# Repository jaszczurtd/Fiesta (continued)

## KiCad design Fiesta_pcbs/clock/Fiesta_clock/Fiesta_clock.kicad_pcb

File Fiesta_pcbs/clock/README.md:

# Fiesta_clock PCB

[Polski](README.pl.md)

A 70 × 70 mm carrier for RP2040-Zero, CAN and DS3231 Mini. Firmware defaults to a different
RTC, so select the board variant deliberately.

## Before connecting

- Use USB or vehicle power, never both at once.
- Select the DS3231 firmware variant for this board. The default firmware selects PCF8563.
- R9/R10 are 47 kΩ / 10 kΩ; the firmware voltage conversion still needs the corresponding update.
- Check regulator temperature, supply stability, RTC header orientation and battery arrangement on the prototype.

## Assembly and startup

The [assembly reference](ASSEMBLY.md) contains schematics, previews, connectors, component
selection and manufacturing requirements. It uses the KiCad project names and numbering.

After checking the hardware, follow the [firmware guide](../../src/Fiesta_clock/README.md).

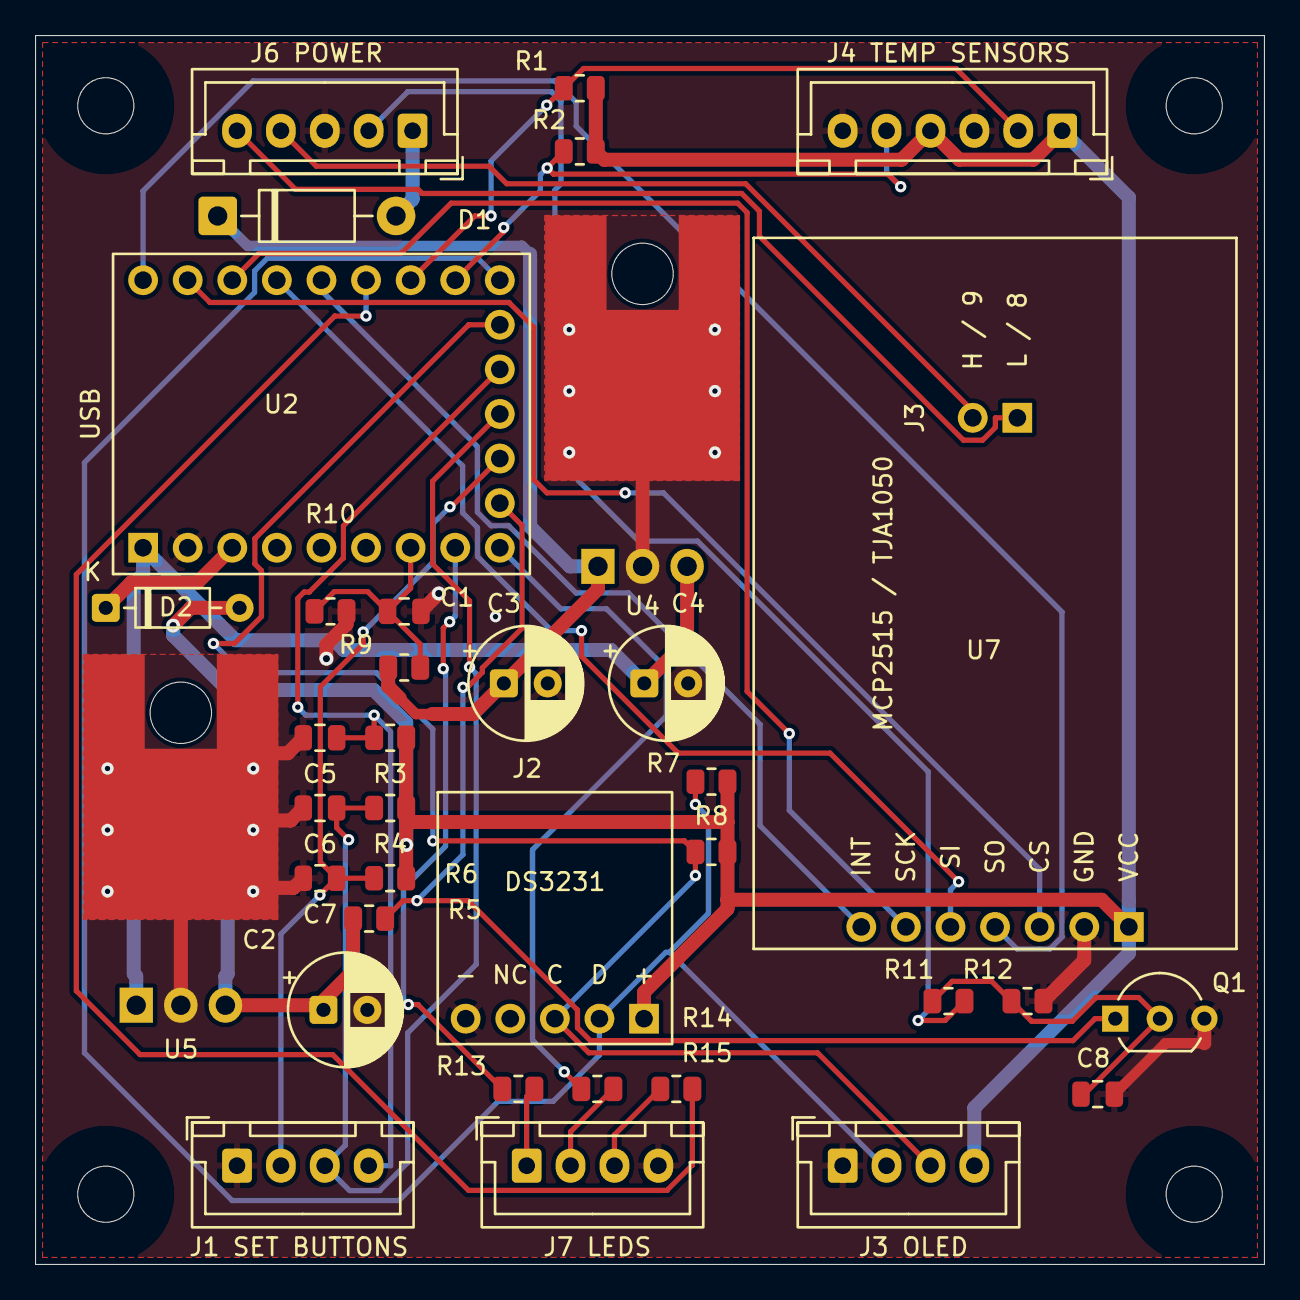
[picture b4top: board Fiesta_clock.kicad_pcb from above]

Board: 2 copper layers, 70.0 x 70.0 mm, 40 parts (0 on the bottom side), 30 nets.

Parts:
C1, C5, C6, C7, C8: 100nF; C_0805_2012Metric
C2, C3, C4: 4,7uF; CP_Radial_D6.3mm_P2.50mm
D1: 1N4007; D_DO-41_SOD81_P10.16mm_Horizontal
D2: BAT48RL; D_DO-35_SOD27_P7.62mm_Horizontal
H1, H2, H3, H4: MountingHole_3.2mm_M3
J1: Set-buttons; JST_XH_B4B-XH-A_1x04_P2.50mm_Vertical
J2: DS3231 Mini; DS3231_Mini_13x14mm_1x05_P2.54mm
J3: OLED module; JST_XH_B4B-XH-A_1x04_P2.50mm_Vertical
J4: temp-sensors; JST_XH_B6B-XH-A_1x06_P2.50mm_Vertical
J6: Power; JST_XH_B5B-XH-A_1x05_P2.50mm_Vertical
J7: LEDs; JST_XH_B4B-XH-A_1x04_P2.50mm_Vertical
Q1: BC547; TO-92_Inline_Wide
R1, R2, R3, R4, R5, R6, R7, R8, R11: 4k7; R_0805_2012Metric
R9: 47k; R_0805_2012Metric
R10, R12: 10k; R_0805_2012Metric
R13, R14, R15: 470R; R_0805_2012Metric
U2: RP2040-Zero; RP2040-Zero_THT
U4: L7805; TO-220-3_Horizontal_TabDown_GND
U5: LM2931-3.3; TO-220-3_Horizontal_TabDown_GND
U7: MCP2515_CAN; MCP2515_TJA1050_Module_J3_40x27mm

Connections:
GND: C1.2, C2.2, C3.2, C4.2, C5.2, C6.2, C7.2, C8.2, J1.1, J2.5, J3.1, J4.3, J4.6, J6.3, J7.4, Q1.3, R10.2, R12.2, U2.2, U4.2, U5.2, U7.2
unnamed: D1.2, J6.1
unnamed: C3.1, D1.1, R9.1, U4.1
unnamed: C2.1, D2.2, J2.1, J3.4, J4.1, J4.4, R1.2, R2.2, R3.1, R4.1, R5.1, R6.1, R7.2, R8.2, U5.3, U7.1
unnamed: D2.1, U2.3
unnamed: C7.1, J1.2, R5.2, U2.20
unnamed: C6.1, J1.3, R4.2, U2.21
unnamed: C5.1, J1.4, R3.2, U2.22
unnamed: J2.3, J3.3, R8.1, U2.23
unnamed: J2.2, J3.2, R7.1, U2.18
unnamed: J4.2, R1.1, U2.16
unnamed: J4.5, R2.1, U2.17
unnamed: J6.2, R11.2
unnamed: J6.4, U7.9
unnamed: J6.5, U7.8
unnamed: J7.1, R13.2
unnamed: J7.2, R14.2
unnamed: J7.3, R15.1
unnamed: C8.1, Q1.2, R11.1, R12.1
unnamed: Q1.1, R6.2, U2.19
unnamed: C4.1, U2.1, U4.3, U5.1
unnamed: U2.10, U7.4
unnamed: U2.11, U7.3
unnamed: U2.12, U7.6
unnamed: U2.13, U7.5
unnamed: U2.14, U7.7
unnamed: R15.2, U2.15
unnamed: R14.1, U2.9
unnamed: R13.1, U2.8
unnamed: C1.1, R9.2, R10.1, U2.7

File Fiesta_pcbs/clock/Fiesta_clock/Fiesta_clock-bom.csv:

"Reference","Value","Footprint","Quantity"
"C1","100nF","Capacitor_SMD:C_0805_2012Metric","1"
"C2","4,7uF","Capacitor_THT:CP_Radial_D6.3mm_P2.50mm","1"
"C3","4,7uF","Capacitor_THT:CP_Radial_D6.3mm_P2.50mm","1"
"C4","4,7uF","Capacitor_THT:CP_Radial_D6.3mm_P2.50mm","1"
"C5","100nF","Capacitor_SMD:C_0805_2012Metric","1"
"C6","100nF","Capacitor_SMD:C_0805_2012Metric","1"
"C7","100nF","Capacitor_SMD:C_0805_2012Metric","1"
"C8","100nF","Capacitor_SMD:C_0805_2012Metric","1"
"D1","1N4007","Diode_THT:D_DO-41_SOD81_P10.16mm_Horizontal","1"
"D2","BAT48RL","Diode_THT:D_DO-35_SOD27_P7.62mm_Horizontal","1"
"J1","Set-buttons","Connector_JST:JST_XH_B4B-XH-A_1x04_P2.50mm_Vertical","1"
"J2","DS3231 Mini","FiestaClock:DS3231_Mini_13x14mm_1x05_P2.54mm","1"
"J3","OLED module","Connector_JST:JST_XH_B4B-XH-A_1x04_P2.50mm_Vertical","1"
"J4","temp-sensors","Connector_JST:JST_XH_B6B-XH-A_1x06_P2.50mm_Vertical","1"
"J6","Power","Connector_JST:JST_XH_B5B-XH-A_1x05_P2.50mm_Vertical","1"
"J7","LEDs","Connector_JST:JST_XH_B4B-XH-A_1x04_P2.50mm_Vertical","1"
"Q1","BC547","Package_TO_SOT_THT:TO-92_Inline_Wide","1"
"R1","4k7","Resistor_SMD:R_0805_2012Metric","1"
"R2","4k7","Resistor_SMD:R_0805_2012Metric","1"
"R3","4k7","Resistor_SMD:R_0805_2012Metric","1"
"R4","4k7","Resistor_SMD:R_0805_2012Metric","1"
"R5","4k7","Resistor_SMD:R_0805_2012Metric","1"
"R6","4k7","Resistor_SMD:R_0805_2012Metric","1"
"R7","4k7","Resistor_SMD:R_0805_2012Metric","1"
"R8","4k7","Resistor_SMD:R_0805_2012Metric","1"
"R9","47k","Resistor_SMD:R_0805_2012Metric","1"
"R10","10k","Resistor_SMD:R_0805_2012Metric","1"
"R11","4k7","Resistor_SMD:R_0805_2012Metric","1"
"R12","10k","Resistor_SMD:R_0805_2012Metric","1"
"R13","470R","Resistor_SMD:R_0805_2012Metric","1"
"R14","470R","Resistor_SMD:R_0805_2012Metric","1"
"R15","470R","Resistor_SMD:R_0805_2012Metric","1"
"U2","RP2040-Zero","Adjustometer:RP2040-Zero_THT","1"
"U4","L7805","FiestaClock:TO-220-3_Horizontal_TabDown_GND","1"
"U5","LM2931-3.3","FiestaClock:TO-220-3_Horizontal_TabDown_GND","1"
"U7","MCP2515_CAN","FiestaFootprints:MCP2515_TJA1050_Module_J3_40x27mm","1"

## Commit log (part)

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2026-04-22 feat(CI) more unit tests for adjustometer, make the code more testable.
2026-04-23 CI fix
2026-04-23 feat(CI) new tests for OilAndSpeed module
2026-04-23 README update
2026-04-23 feat(serial,docs,usb): complete Phase 0 bootstrap — HELLO identity, per-module USB iProduct, Serial Configurator in architecture
    - migrate ECU, Clocks, OilAndSpeed config wrappers to the extended
    hal_serial_session_init(session, module_tag, fw_version, build_id) API;
    configSessionTick no longer passes the module tag
    - add FW_VERSION and BUILD_ID defaults to each module's config.h, both
    overridable via -D for build-system injection of a git SHA
    - per-module USB iProduct override via arduino-cli --build-property
2026-04-24 feat(docs): readme and images update
2026-04-24 feat(tests): harden Clocks/OilAndSpeed CAN
    - Clocks/OilAndSpeed CAN RX hardening (ports ECU f8ab7c9): reject
    NULL/oversized frames and do per-case length checks in onCanFrame
    before dereferencing payload; OilAndSpeed canSendLoop drops the
    outer static-var dedup so heartbeat stays regular, matching ECU's
    CAN_updaterecipients_0x pattern
    - tests: new Clocks/tests/test_can.cpp and OilAndSpeed/tests/test_can.cpp
2026-04-24 - CI fix: Clocks workflow now clones canDefinitions (needed by the new test_can) matching the OilAndSpeed workflow; Clocks CMakeLists defines CANDEFS and injects it into clocks_mock includes so all c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
2026-04-24 feat(CI): verify Fiesta firmware build wrappers
    - add a dedicated workflow for ECU, Clocks, OilAndSpeed, and Adjustometer
    - run arduino-build.sh build/debug and refresh-intellisense.sh for each module
    - install arduino-cli + rp2040 core and clone JaszczurHAL/canDefinitions in CI
    - trigger the workflow for module changes and shared src/common/scripts changes
2026-04-24 chore(SerialConfigurator): gitignore build_ci/ and untrack accidentally committed CI build artifacts
    build_ci/ is the CMake build directory used by
    .github/workflows/serial-configurator-tests.yml. It was missing from
    the module's .gitignore (which only covered the local /build/), so
    the first CI-style local run in 2bc32bf committed Makefile,
    DartConfiguration.tcl, CTest temp logs, and the .a/ELF binaries.
    Add /build_ci/ to .gitignore and untrack the leaked files via
2026-04-25 chore(SerialConfigurator): gitignore build_ci/ and untrack accidentally committed CI build artifacts
    build_ci/ is the CMake build directory used by
    .github/workflows/serial-configurator-tests.yml. It was missing from
    the module's .gitignore (which only covered the local /build/), so
    the first CI-style run in 60dd535 committed Makefile,
    DartConfiguration.tcl, CTest temp logs, and the .a/ELF binaries.
    Add /build_ci/ to .gitignore and untrack the leaked files via
2026-04-25 feat(config): merge ecuParams into config and switch default board to RP2040-Plus
    - move runtime ECU params into config.c/h (validation, staging/apply, KV persistence with CRC32)
    - reorganize config.h into NON-TWEAKABLE and TWEAKABLE sections with grouped bounds per parameter
    - add NOMINAL_RPM_VALUE as tweakable and use runtime getters in rpm, fan, and heater logic
    - initialize ecu params at startup and increase RP2040 EEPROM emulation size to 32KB
    - add unit tests for ecu params (defaults, persistence, malformed blob fallback, validation rules)
    - expose test-only ecu params helpers under UNIT_TEST to keep Werror builds clean
2026-04-26 fix(ui): speed up auto metadata refresh and remove redundant subtitle, README update
2026-04-26 feat(SerialConfigurator): add SHA-256 + HMAC-SHA256 primitives (Phase 3 prep)
    - sc_crypto.h: extend API with sha256/hmac_sha256 (+_hex variants).
    - sc_sha256.c: portable FIPS 180-4 SHA-256 + RFC 2104 HMAC-SHA256,
    compiled by both backends (JaszczurHAL hal_crypto does not expose
    these primitives; the 'none' backend would otherwise leave CI without
    hashing).
    - test_sc_crypto_bridge: vectors from FIPS 180-2 (sha256) and RFC 4231
2026-04-27 feat(SerialConfigurator): host orchestration + CLI for SC_REBOOT_BOOTLOADER (Phase 5)
    - sc_core: sc_core_authenticate + sc_core_reboot_to_bootloader. The
    authenticator parses uid/session from HELLO and runs SC_AUTH_BEGIN +
    SC_AUTH_PROVE via the existing transport seam. ScAuthStatus and
    ScRebootStatus carry stable tokens for log/CLI consumability.
    - CLI: reboot-bootloader subcommand with selectors (--module/--uid/
    --port) and optional Phase 4 preflight (--manifest/--artifact). Hard
2026-04-27 feat(SerialConfigurator): per-module Flash sections + UF2 check + path persistence (Phase 6.2)
    - New sc_flash.{h,c}: host-side UF2 format checker (magic1/2 + end
    magic, RP2040 family id, block alignment, total-blocks consistency).
    - New sc_flash_paths.{h,c}: JSON persistence for the per-module Flash
    picker paths so the GUI remembers selections across runs.
    - Flash tab gains per-module sections gated by lamp/ID state;
    EN+PL i18n keys added in the same change set.
2026-04-27 fix(common): split sc_protocol.h to keep fiesta_sc_definitions HAL-free
    CI host runners fall back to sc_crypto_none when JaszczurHAL is not
    on their include path; the R1.1 fiesta_sc_definitions library hard-
    required hal/hal_serial_session_vocabulary.h via sc_protocol.h and
    broke that build.
    - Move fiesta_default_vocabulary out of sc_protocol.h into a new
    sc_session_vocabulary.h that pulls the JHAL header. Firmware
2026-04-27 refactor(Clocks,OilAndSpeed): migrate config.cpp onto sc_param descriptor framework (R1.4 + R1.5)
    - Clocks: 283 → 214 LOC (-24%); six thermal thresholds declared
    as SC_PARAM_SCALAR_I16_RO_NOT_PERSISTED descriptors over a
    static const clocks_values_t mirror struct.
    - OilAndSpeed: 279 → 194 LOC (-30%); two read-only sampling
    intervals declared the same way.
    - Both modules switch to fiesta_default_vocabulary at session
2026-04-27 feat(SerialConfigurator): UF2 copy with progress + re-enumeration waiter (Phase 6.4)
    - sc_flash_copy_uf2(src, drive, progress_cb, ...): reads 64 KiB
    chunks, writes <drive>/firmware.uf2, invokes progress callback
    per chunk, fflush + fsync before returning so the kernel actually
    flushes to mass storage. Source size capped at SC_FLASH_UF2_MAX_BYTES;
    callers should run sc_flash_uf2_format_check first.
    - sc_flash_wait_reenumeration(uid_hex, timeout_ms, ...): polls
2026-04-27 debug(SerialConfigurator) investigate problems with flashing pico devices
2026-04-28 fix(progressbar) added a kind of a custom progressbar, since the build in does not work so well.
2026-04-28 feat(vsc): added default keybindings for vscode
2026-04-28 feat(documentation): changes in project documentation reflects the last refactor
2026-04-29 feat(scDefinitions): SC SET_PARAM wire vocabulary + staging helpers
    - inbound commands SC_CMD_SET_PARAM ("SC_SET_PARAM <id> <v>"),
    SC_CMD_COMMIT_PARAMS, SC_CMD_REVERT_PARAMS
    - status SC_STATUS_COMMIT_FAILED ("SC_COMMIT_FAILED")
    - reply tags PARAM_SET / PARAMS_COMMITTED / PARAMS_REVERTED
    - format strings SC_REPLY_PARAM_SET_FMT
    ("SC_OK PARAM_SET id=%s staged=%d active=%d"),
2026-04-29 fix(CI): remove pull of no longer exiting canDefinitions repo
2026-04-29 feat(SerialConfigurator): Values tab + descriptor `group` cross-cut (Phase 8.6)
    Cross-cutting refactor:
    - sc_param_descriptor_t gains 'const char *group' (snake_case wire
    token); both SC_PARAM_SCALAR_I16 builders take a trailing group_str.
    - SC_REPLY_PARAM_FMT extended with 'group=%s'. Empty/NULL group emits
    "general" so the host parser never sees `key=` with empty value.
    - ScParamDetailData + sc_core_parse_param_result handle the new key.
2026-04-29 fix(SerialConfigurator): improvements regarding CRC fails
2026-05-01 feat(schems): ECU schem WIP, some new screenshots
2026-05-04 feat(schems, legacy): refresh ECU KiCad project, add custom module libraries, and archive old legacy sketches
    - update ECU schematic/project files and regenerate project PDF
    - add custom KiCad footprint library (MCP2515, GY-NEO6MV2, OBD2 J1962)
    - add matching KiCad symbol library entries
    - remove obsolete legacy sources and replace them with archived zip bundles
    - next release (1.1.0)
2026-05-06 misc(docs): Add documentation for OBD-2 communication standards
    Added a comment block explaining the implementation of diagnostic communication standards and its purpose,
    added some screenshots - Fordiag OBD-2 session example
2026-05-09 feat(SerialConfigurator, bootstrap, docs): add DEB packaging flow and generate .deb in bootstrap
    - add package/deb build mode with desktop launcher and icon packaging
    - run build + test + package in bootstrap, with SKIP_DESKTOP_PACKAGE override
    - refresh README and changelog/context notes
2026-05-10 fix(ECU, tests): use ADC supply voltage when VP37 is disabled and cover ECU_UPDATE_01 volts CAN payload
2026-05-10 fix(adc): remove EMA filtering from ECU supply voltage measurement
2026-05-12 feat(rpm): initial version of PI controller for non-vp37 rpm adjustement
2026-05-22 fix(Clocks, ECU, OilAndSpeed): switch cluster pulse output to persistent HAL timers and disable DS18B20
2026-05-25 feat(Fiesta_clock, SerialConfigurator, HAL, scripts): promote RTC_Clock to full module and align with shared tooling
    - add RTC CAN broadcast path (CAN_ID_RTC_UPDATE 0x130) in common definitions and Fiesta_clock sender (integrity-gated)
    - integrate Fiesta_clock with SC protocol (META/PARAM_LIST/VALUES/SET/COMMIT/REVERT) and expose rtc_* params + rtc_integrity
    - register RTC_Clock in shared module roster/tokens and wire detection + flash mappings in SerialConfigurator
    - add RTC-specific GUI validation in Values tab (dynamic day range with leap-year handling)
    - replace legacy Fiesta_clock serial monitor scripts with thin wrappers over common fiesta-serial-persistent
    - migrate module HAL configs
2026-05-25 feat(ECU, SerialConfigurator, scripts, docs): add SC_GET_GPS telemetry path with CLI + GUI map tab
    - extend SC protocol with SC_GET_GPS / SC_OK GPS payload for live telemetry
    - add ECU-side GPS snapshot getters and SC command handling in config session flow
    - introduce host sc_gps module (transport wrapper + parser) and expose core send facade
    - add serial-configurator-cli get-gps command with parsed output formatting
    - add GUI Map tab (libshumate-backed, graceful fallback when unavailable)
    - align map polling cadence with ECU GPS refresh interval (4 s)
2026-06-04 fix(compilation): update the codebase to the newest version of JaszczurHAL
2026-06-07 fix(tests): fix for broken tests after JaszczurHAL crypto refactoring
2026-06-22 feat(can): migration to the new CAN API
